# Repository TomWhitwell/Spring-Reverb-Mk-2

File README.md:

## Spring Reverb Mk 2

These are the design files for the Music Thing Modular Spring Reverb. 

[Full details about the module are in this rather long Medium post](https://medium.com/music-thing-modular-notes/everything-i-know-about-spring-reverb-1fb4b32abf87) 

You can [buy full kits for the Spring module here at Thonk](https://www.thonk.co.uk/shop/mtm-spring-reverb-mkii-kit/?utm_source=github), and [here's the kit for the expander](https://www.thonk.co.uk/shop/mtm-spring-expander-kit/?utm_source=github). 

# Issues and troubleshooting 
The quickest way to find solutions or report issues is [here in the issue log](https://github.com/TomWhitwell/Spring-Reverb-Mk-2/issues)

# In this repository you will find: 

[The Schematic PDF is here](https://github.com/TomWhitwell/Spring-Reverb-Mk-2/raw/master/Collateral/SpringReverbMk2-Schematic.pdf) 

Eagle CAD PCB files for:  
1. The main module, which contains two PCBs in the same file: SpringReverbRev2_combined
2. A plain PCB panel for the main module: SpringReverbRev2_panel
3. The PCB for the expander: Spring_Rev2_expander
4. A plan PCB panel for the expander: Spring_Rev2_expander_panel

The draft BOM is [here on google drive](https://docs.google.com/spreadsheets/d/1CzZeQc7hFVf5DQ_6vUL5soYb9Bh4oqvPB2Zx_D7NQ_I/edit?usp=sharing)

# License

Spring is Open Hardware
All hardware and software design in this project is Creative Commons licensed by Tom Whitwell: CC-BY-SA: Attribution / ShareAlike
If you use any work in this project, you should credit me, and you must republish any changes you make under the same license.
This license does permit commercial use of these designs, but consider getting in touch before selling anything.
This license does not permit you to use the name Music Thing Modular. Please do not use the name 'Spring' or 'Music Thing Modular' for any derivative works.

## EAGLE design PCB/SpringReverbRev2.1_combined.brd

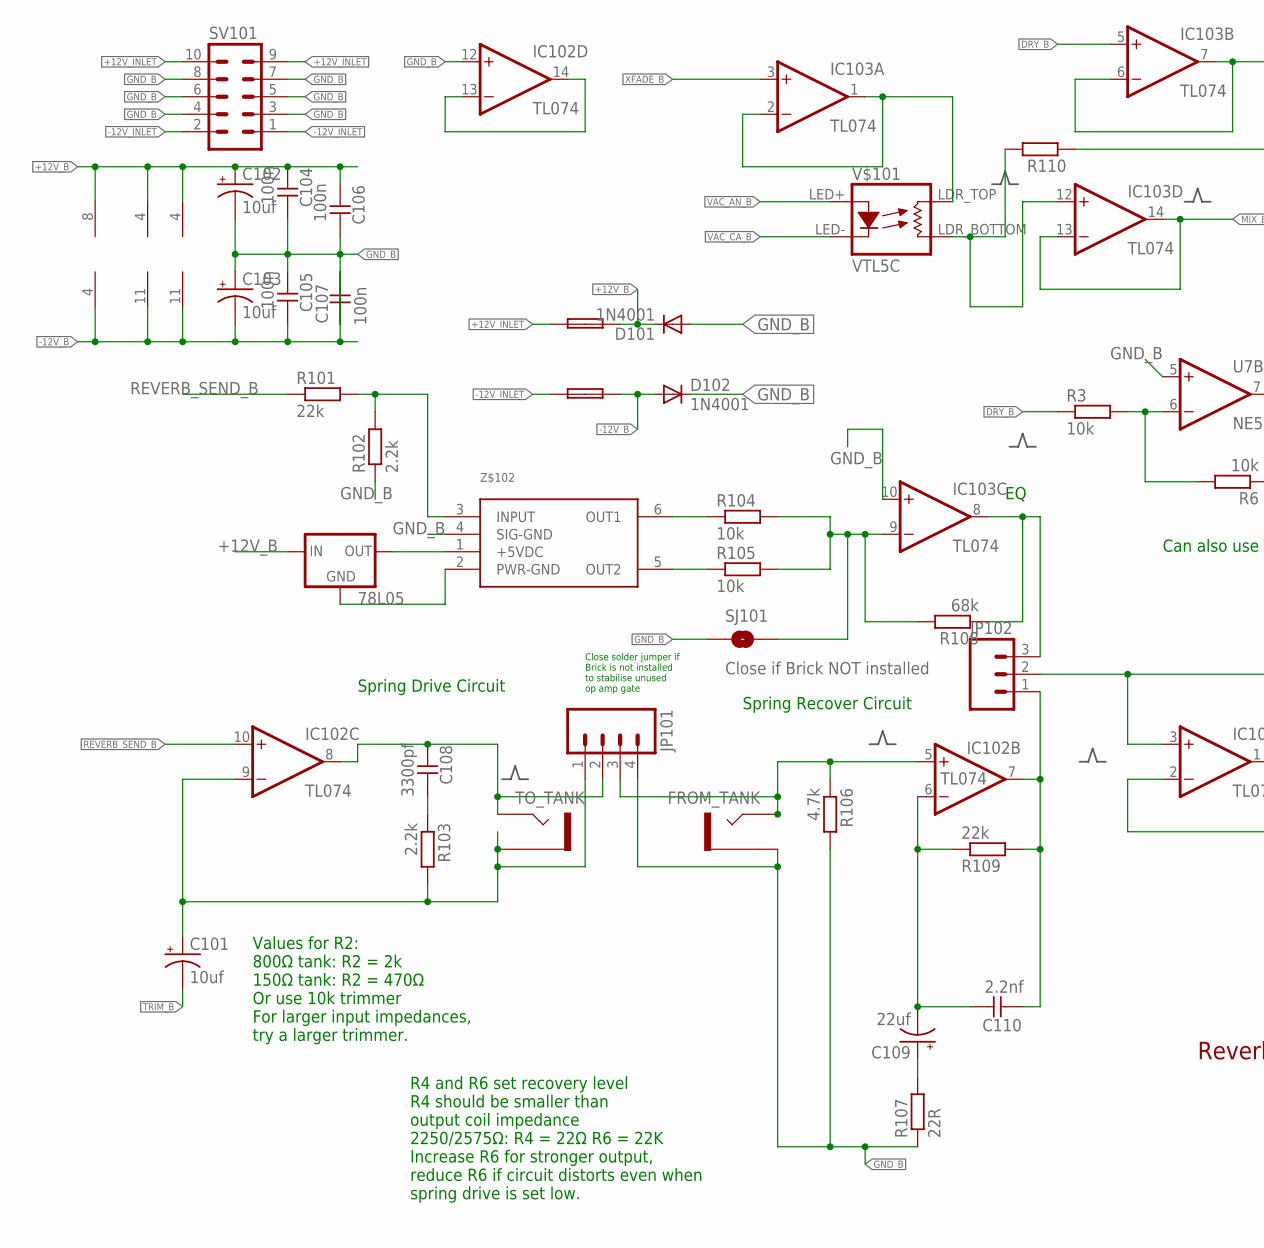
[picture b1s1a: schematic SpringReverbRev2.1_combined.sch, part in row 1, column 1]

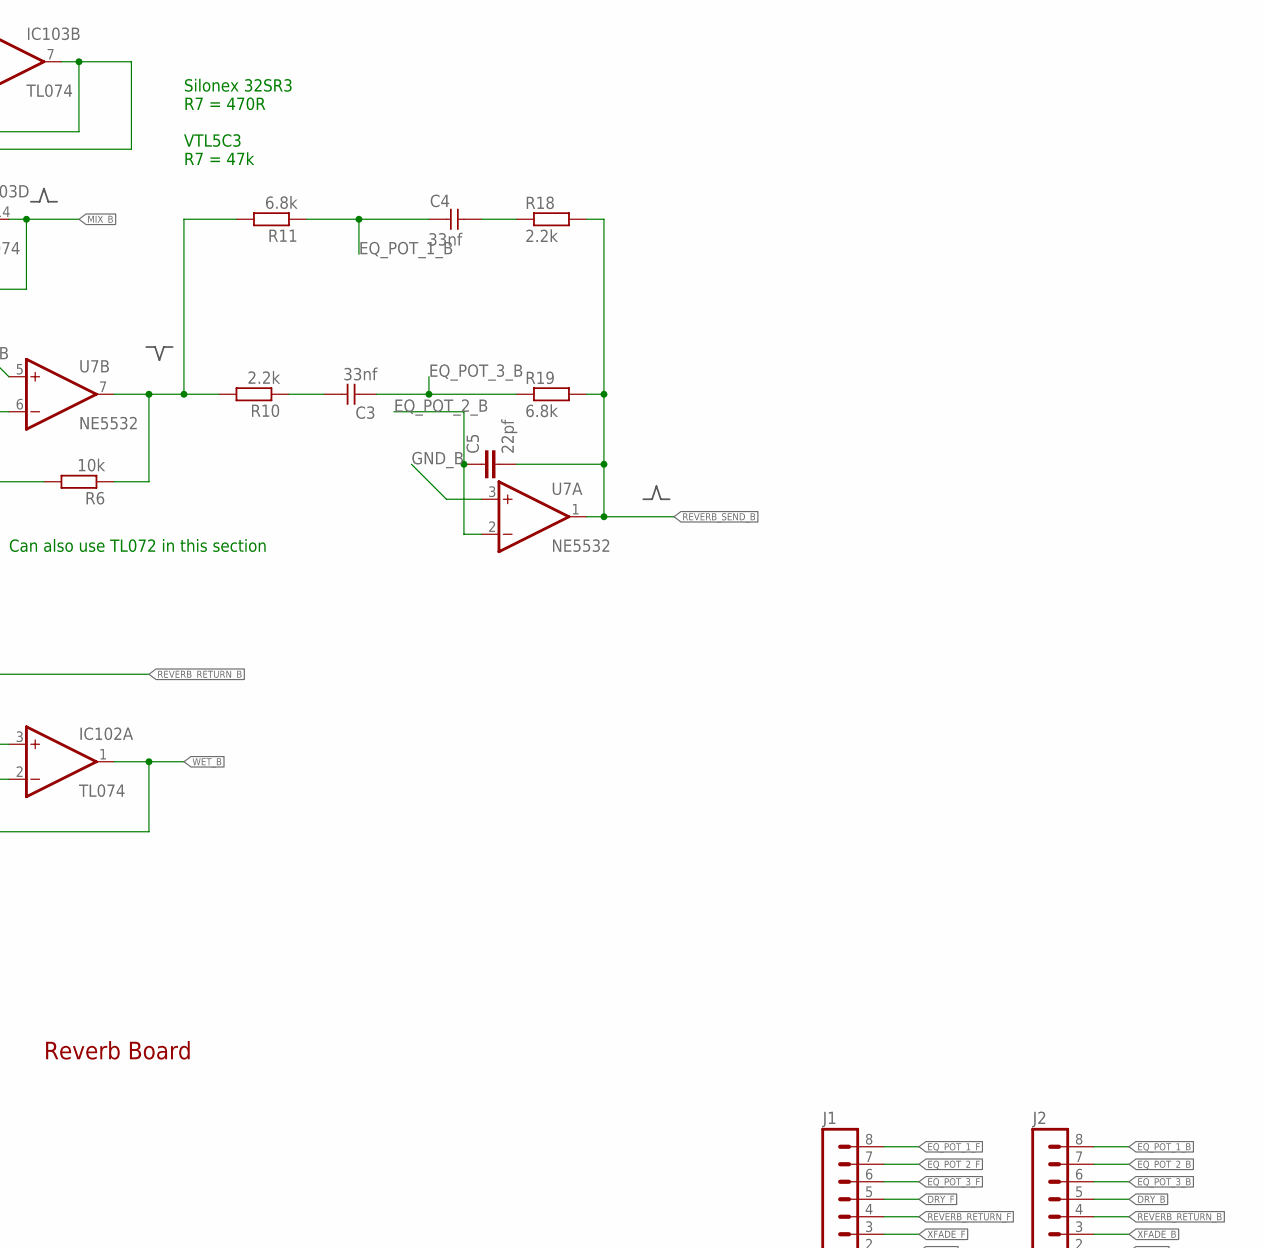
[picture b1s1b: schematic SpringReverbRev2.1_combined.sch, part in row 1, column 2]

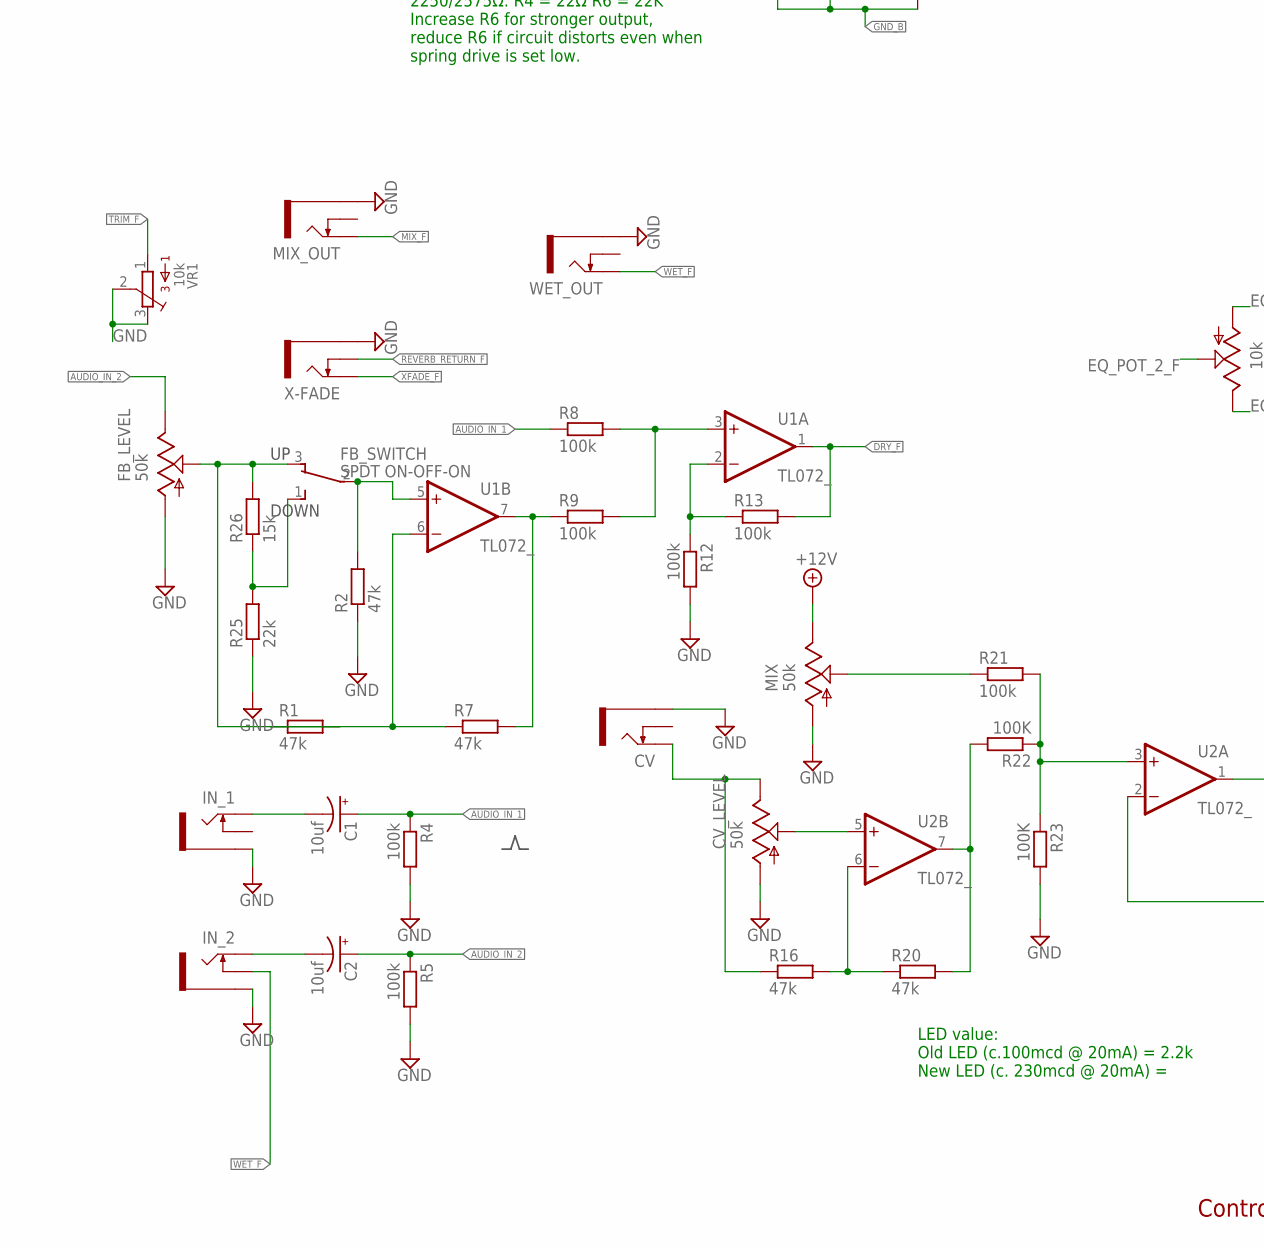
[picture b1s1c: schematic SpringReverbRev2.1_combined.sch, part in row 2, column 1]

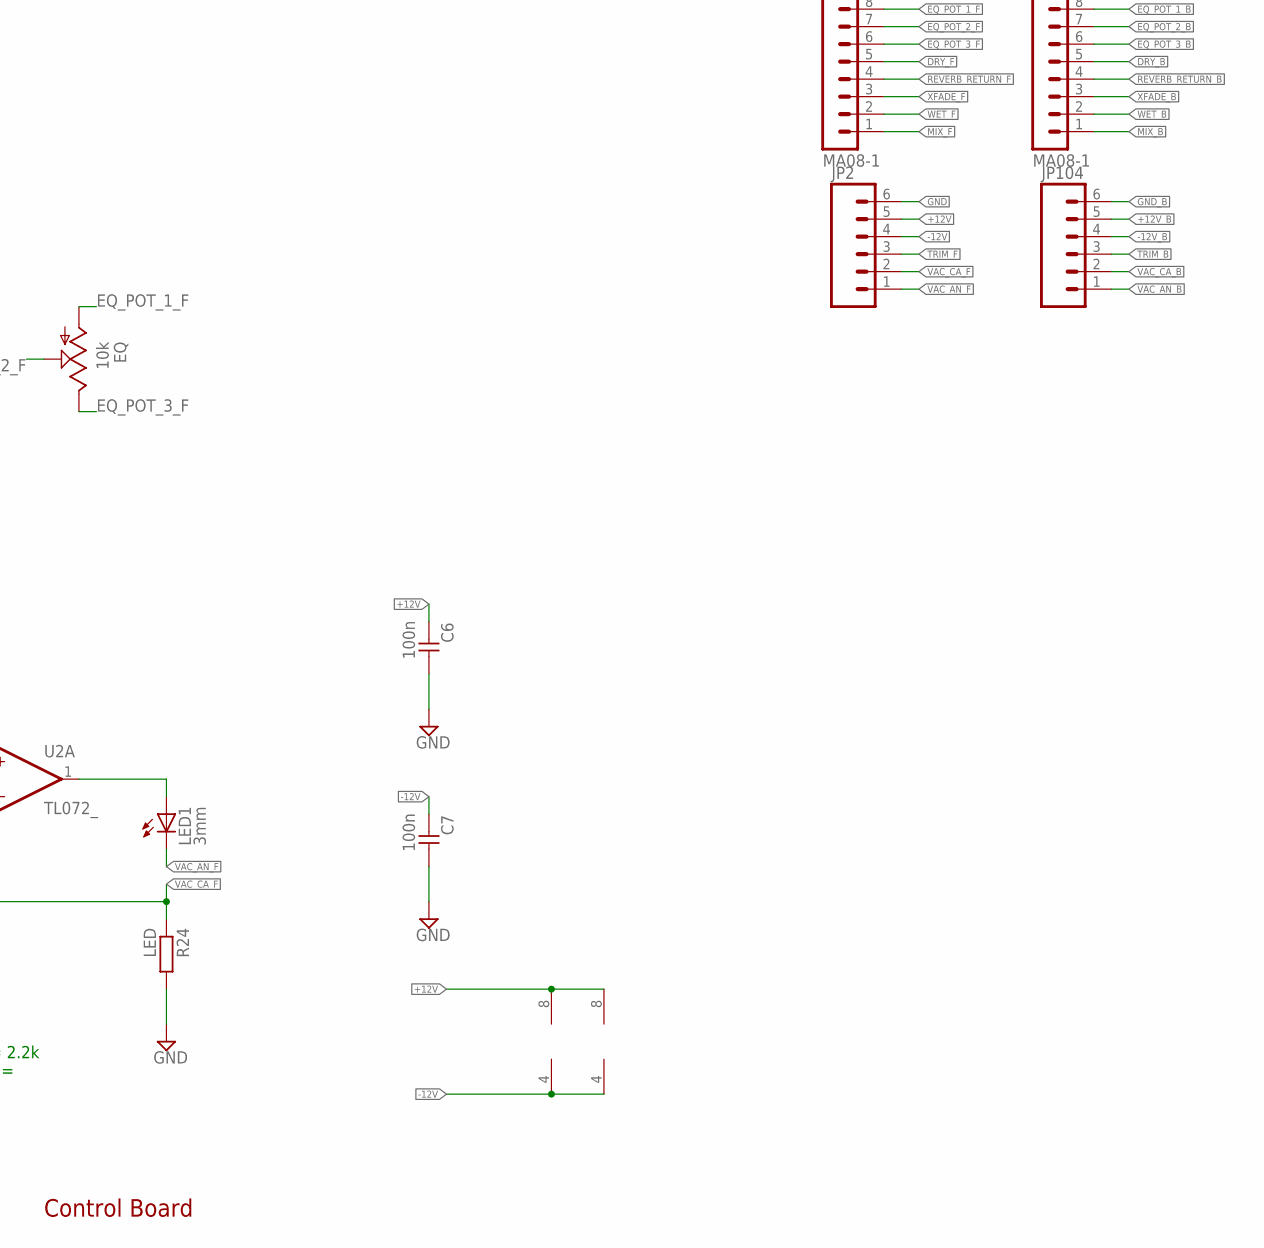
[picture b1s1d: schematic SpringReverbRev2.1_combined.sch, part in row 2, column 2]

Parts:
78L05: 78LXX
C1, C2: 10uf; 050_020
C3, C4: 33nf; C050-024X044
C5: 22pf; 050X030_025
C6, C7, C104, C105, C106, C107: 100n; C050-024X044
C101, C102, C103: 10uf; CPOL-RADIAL-10UF-25V
C108: 3300pf; C050-024X044
C109: 22uf; CPOL-RADIAL-10UF-25V
C110: 2.2nf; C050-024X044
CV: THONKICONNNEW; WQP-PJ301M-12_JACK
CV_LEVEL: 50k; EVUF
D101, D102: 1N4001; DO41-10
EQ: 10k; EVUF
F101, F102: FUSE; C050H075X075
FB_LEVEL: 50k; EVUF
FB_SWITCH: SPDT ON-OFF-ON; SPDT-VERTICAL-TOP-SUBMINI-MULTICOMP
FROM_TANK: CUI-RCJ_RCA_PHONO
IC102, IC103: TL074; DIL14
IN_1, IN_2: THONKICONNNEW; WQP-PJ301M-12_JACK
J1, J2: MA08-1
JP2, JP104: M06SIP; 1X06
JP101: M04POLAR; MOLEX-1X4
JP102: M03LOCK_NO_SILK; 1X03_LOCK_NO_SILK
LED1: 3mm; LED3MM
MIX: 50k; EVUF
MIX_OUT: THONKICONNNEW; WQP-PJ301M-12_JACK
R1, R2, R7, R16, R20: 47k; 7MM_RESISTOR
R3, R6, R104, R105: 10k; 7MM_RESISTOR
R4, R5, R8, R9, R12, R13, R21: 100k; 7MM_RESISTOR
R10, R18, R102, R103: 2.2k; 7MM_RESISTOR
R11, R19: 6.8k; 7MM_RESISTOR
R22, R23: 100K; 7MM_RESISTOR
R24: LED; 7MM_RESISTOR
R25, R101, R109: 22k; 7MM_RESISTOR
R26: 15k; 7MM_RESISTOR
R106: 4.7k; 7MM_RESISTOR
R107: 22R; 7MM_RESISTOR
R108: 68k; 7MM_RESISTOR
R110: RESISTOR7MM; 7MM_RESISTOR
SJ101: Close if Brick NOT installed; SJ_2S-NOTRACE
SV101: 10_PIN_HEADER; MA05-2
TO_TANK: CUI-RCJ_RCA_PHONO
U1, U2: TL072_; DIL08
U7: NE5532; DIL08
V$101: VTL5C; VACTROL_COMPACT
VR1: 10k; BOURNS_3362P_TRIMMER
WET_OUT: THONKICONNNEW; WQP-PJ301M-12_JACK
X-FADE: THONKICONNNEW; WQP-PJ301M-12_JACK
Z$102: BTDR-2H

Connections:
+12V: C6.2, JP2.5, MIX.3 (E), U1.8 (V+), U2.8 (V+)
+12V_B: 78L05.IN, C102.1 (+), C104.2, C106.2, D101.C, F101.1, IC102.4 (V+), IC103.4 (V+), JP104.5, U7.8 (V+)
+12V_INLET: F101.2, SV101.9, SV101.10
-12V: C7.2, JP2.4, U1.4 (V-), U2.4 (V-)
-12V_B: C103.2 (-), C105.1, C107.1, D102.A, F102.1, IC102.11 (V-), IC103.11 (V-), JP104.4, U7.4 (V-)
-12V_INLET: F102.2, SV101.1, SV101.2
AUDIO_IN_1: C1.+, R4.1, R8.1
AUDIO_IN_2: C2.+, FB_LEVEL.3 (E), R5.1
AUDIO_IN_BUF: IC103.6 (-IN), IC103.7 (OUT), R110.1
BRK: IC103.8 (OUT), JP102.3, R108.1
CV_F: R20.2, R22.2, U2.7 (OUT)
DRY_B: IC103.5 (+IN), J2.5, R3.1
DRY_F: J1.5, R13.2, U1.1 (OUT)
EQ_POT_1_B: C4.2, J2.8, R11.1
EQ_POT_1_F: EQ.1 (A), J1.8
EQ_POT_2_B: C5.1, J2.7, U7.2 (-IN)
EQ_POT_2_F: EQ.2 (S), J1.7
EQ_POT_3_B: C3.2, J2.6, R19.1
EQ_POT_3_F: EQ.3 (E), J1.6
GND: C6.1, C7.1, CV.P$3_SLEEVE (SLEEVE), CV_LEVEL.1 (A), FB_LEVEL.1 (A), IN_1.P$3_SLEEVE (SLEEVE), IN_2.P$3_SLEEVE (SLEEVE), JP2.6, MIX.1 (A), MIX_OUT.P$3_SLEEVE (SLEEVE), R2.1, R4.2, R5.2, R12.2, R23.2, R24.2, R25.1, VR1.2, VR1.3, WET_OUT.P$3_SLEEVE (SLEEVE), X-FADE.P$3_SLEEVE (SLEEVE)
GND_B: C102.2 (-), C103.1 (+), C104.1, C105.2, C106.1, C107.2, D101.A, D102.C, FROM_TANK.GND1 (SLEEVE), FROM_TANK.GND2 (SLEEVE), IC102.12 (+IN), IC103.10 (+IN), JP101.4, JP104.6, R102.1, R106.2, R107.1, SJ101.1, SV101.3, SV101.4, SV101.5, SV101.6, SV101.7, SV101.8, U7.3 (+IN), U7.5 (+IN), Z$102.4 (SIG-GND)
MIX_B: IC103.13 (-IN), IC103.14 (OUT), J2.1
MIX_F: J1.1, MIX_OUT.P$1_TIP (TIP)
unnamed: C1.-, IN_1.P$1_TIP (TIP)
unnamed: C2.-, IN_2.P$1_TIP (TIP)
unnamed: MIX.2 (S), R21.1
unnamed: FB_LEVEL.2 (S), FB_SWITCH.3, R1.2, R26.2
unnamed: R1.1, R7.1, U1.6 (-IN)
unnamed: R7.2, R9.1, U1.7 (OUT)
unnamed: R8.2, R9.2, U1.3 (+IN)
unnamed: R21.2, R22.1, R23.1, U2.3 (+IN)
unnamed: R12.1, R13.1, U1.2 (-IN)
unnamed: CV.P$1_TIP (TIP), CV_LEVEL.3 (E), R16.1
unnamed: LED1.A, U2.1 (OUT)
unnamed: FB_SWITCH.1, R25.2, R26.1
unnamed: C3.1, R10.1
unnamed: C109.1 (+), R107.2
unnamed: C109.2 (-), C110.1, IC102.6 (-IN), R109.1
unnamed: CV_LEVEL.2 (S), U2.5 (+IN)
unnamed: C4.1, R18.1
unnamed: R16.2, R20.1, U2.6 (-IN)
unnamed: R3.2, R6.2, U7.6 (-IN)
unnamed: C108.1, R103.1
unnamed: 78L05.OUT, Z$102.1 (+5VDC)
unnamed: R104.1, Z$102.6 (OUT1)
unnamed: R105.1, Z$102.5 (OUT2)
unnamed: IC103.9 (-IN), R104.2, R105.2, R108.2, SJ101.2
unnamed: R6.1, R10.2, R11.2, U7.7 (OUT)
unnamed: R101.2, R102.2, Z$102.3 (INPUT)
unnamed: 78L05.GND, Z$102.2 (PWR-GND)
unnamed: IC103.12 (+IN), R110.2, V$101.LDR_BOTTOM (RES2)
unnamed: IC102.13 (-IN), IC102.14 (OUT)
unnamed: FB_SWITCH.2, R2.2, U1.5 (+IN)
R+: FROM_TANK.+V (TIP), IC102.5 (+IN), JP101.3, R106.1
REVERB_RETURN_B: IC102.3 (+IN), J2.4, JP102.2
REVERB_RETURN_F: J1.4, X-FADE.P$2_SWITCH (SWITCH)
REVERB_SEND_B: C5.2, IC102.10 (+IN), R18.2, R19.2, R101.1, U7.1 (OUT)
S+: C101.1 (+), IC102.9 (-IN), JP101.1, R103.2, TO_TANK.GND1 (SLEEVE), TO_TANK.GND2 (SLEEVE)
S-: C108.2, IC102.8 (OUT), JP101.2, TO_TANK.+V (TIP)
SPNG: C110.2, IC102.7 (OUT), JP102.1, R109.2
TRIM_B: C101.2 (-), JP104.3
TRIM_F: JP2.3, VR1.1
VAC_AN_B: JP104.1, V$101.LED+
VAC_AN_F: JP2.1, LED1.K (C)
VAC_CA_B: JP104.2, V$101.LED-
VAC_CA_F: JP2.2, R24.1, U2.2 (-IN)
WET_B: IC102.1 (OUT), IC102.2 (-IN), J2.2
WET_F: IN_2.P$2_SWITCH (SWITCH), J1.2, WET_OUT.P$1_TIP (TIP)
XFADE_B: IC103.3 (+IN), J2.3
XFADE_F: J1.3, X-FADE.P$1_TIP (TIP)
X_FADE_IN: IC103.1 (OUT), IC103.2 (-IN), V$101.LDR_TOP (RES1)

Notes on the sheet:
Control Board
Can also use TL072 in this section
Values for R2: 800Ω tank: R2 = 2k 150Ω tank: R2 = 470Ω Or use 10k trimmer For larger input impedances, try a larger trimmer.
Spring Drive Circuit
R4 and R6 set recovery level R4 should be smaller than output coil impedance 2250/2575Ω: R4 = 22Ω R6 = 22K Increase R6 for stronger output, reduce R6 if circuit distorts even when spring drive is set low.
Spring Recover Circuit
Reverb Board
Silonex 32SR3 R7 = 470R VTL5C3 R7 = 47k
Close solder jumper if Brick is not installed to stabilise unused op amp gate
LED value: Old LED (c.100mcd @ 20mA) = 2.2k New LED (c. 230mcd @ 20mA) =

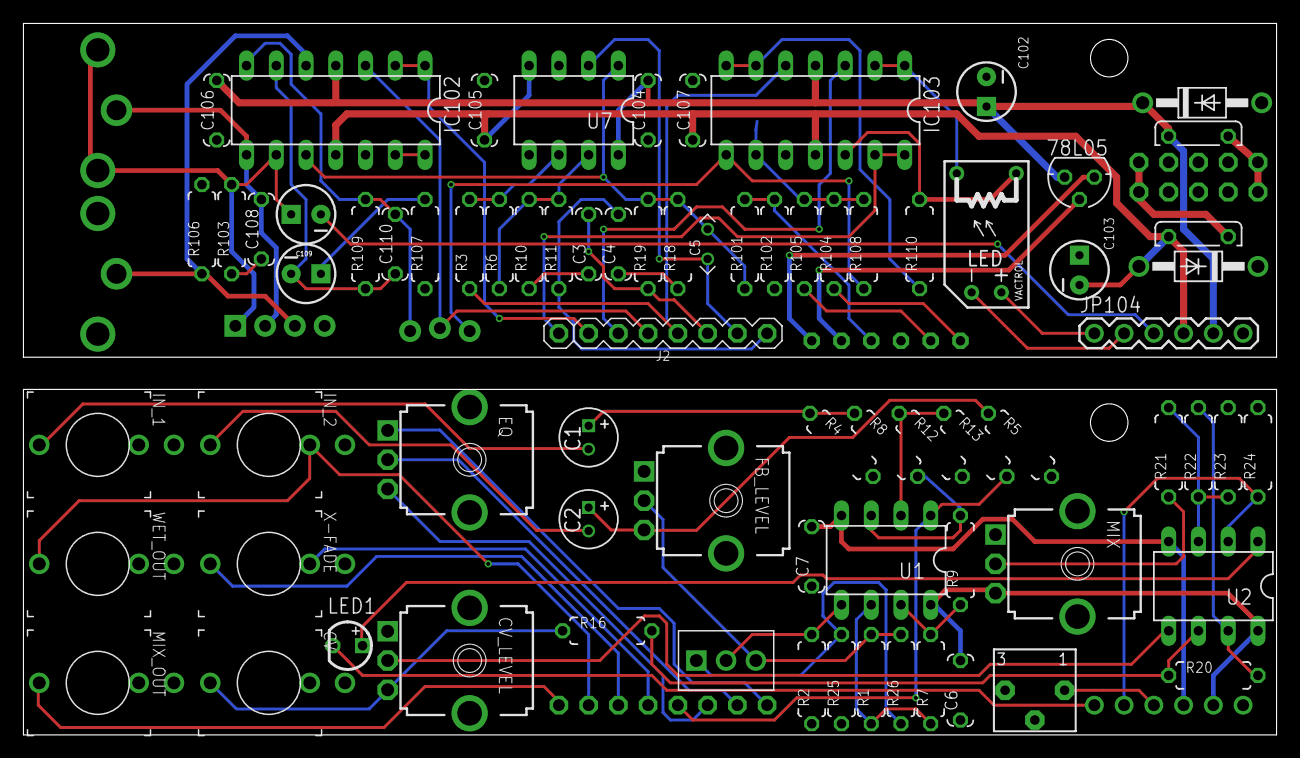
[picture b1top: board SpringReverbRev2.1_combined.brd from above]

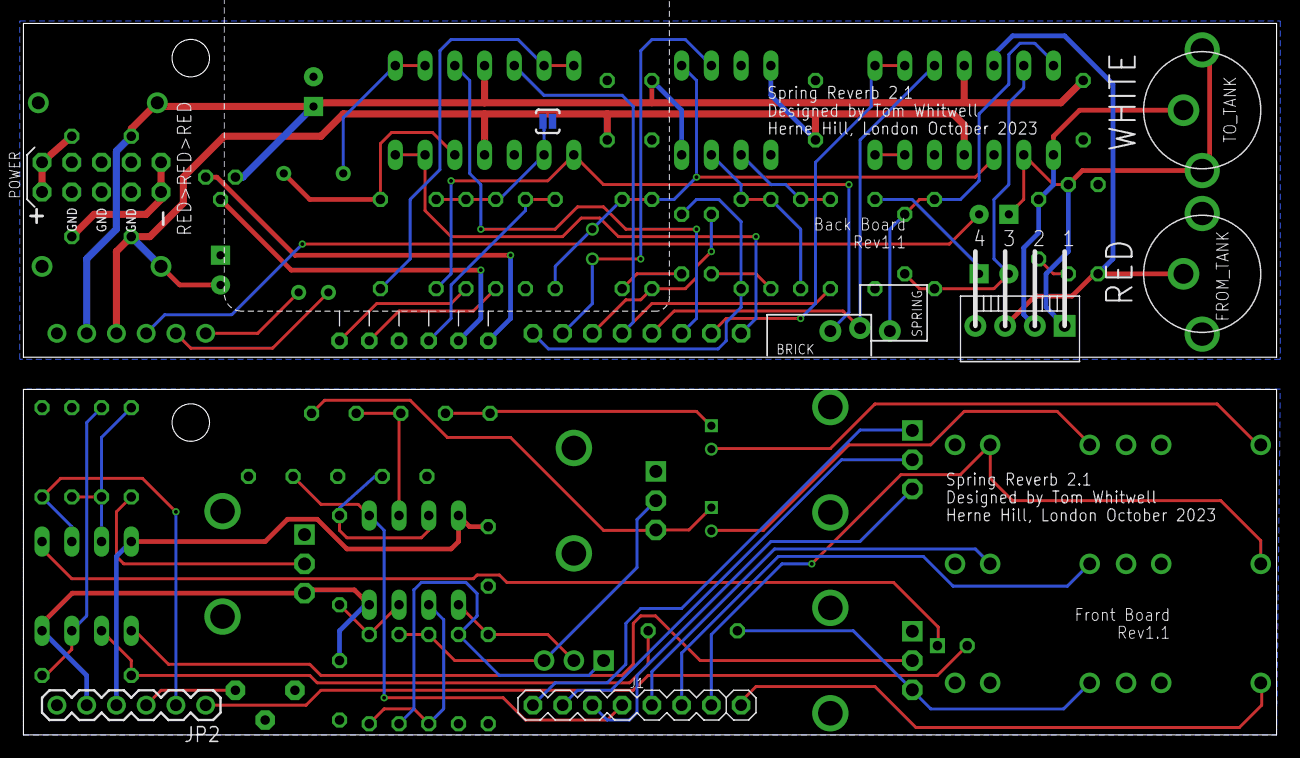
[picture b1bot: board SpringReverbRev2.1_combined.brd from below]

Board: 2 copper layers, 107.0 x 60.8 mm, 87 parts (9 on the bottom side), 71 nets.

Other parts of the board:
U$3, U$4: MOUNTING_HOLE

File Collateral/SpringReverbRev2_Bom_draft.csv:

"Qty";"Value";"Device";"Package";"Parts";"Description";"MF";"MPN";"OC_FARNELL";"OC_NEWARK";"SPICE";
"1";"";"10_PIN_HEADER";"MA05-2";"SV101";"PIN HEADER";"";"";"unknown";"unknown";"";
"1";"";"78LXX";"78LXX";"78L05";"VOLTAGE REGULATOR";"";"";"";"";"";
"1";"";"BTDR-2H";"BTDR-2H";"Z$102";"Accutronics BTDR-2H";"";"";"";"";"";
"1";"";"M03LOCK_NO_SILK";"1X03_LOCK_NO_SILK";"JP102";"Header 3";"";"";"";"";"";
"1";"";"M04POLAR";"MOLEX-1X4";"JP101";"Header 4";"";"";"";"";"";
"2";"";"M06SIP";"1X06";"JP2, JP104";"Header 6";"";"";"";"";"";
"1";"";"RESISTOR7MM";"7MM_RESISTOR";"R110";"Standard resistor, various versions";"";"";"";"";"";
"2";"100K";"RESISTOR7MM";"7MM_RESISTOR";"R22, R23";"Standard resistor, various versions";"";"";"";"";"";
"7";"100k";"RESISTOR7MM";"7MM_RESISTOR";"R4, R5, R8, R9, R12, R13, R21";"Standard resistor, various versions";"";"";"";"";"";
"6";"100n";"C-EU050-024X044";"C050-024X044";"C6, C7, C104, C105, C106, C107";"CAPACITOR, European symbol";"";"";"";"";"";
"1";"10k";"ALPHA-9MMF2A";"EVUF";"EQ";"9 mm Square Rotary Potentiometers";"";"";"";"";"";
"1";"10k";"BOURNS_3362P_TRIMMERP";"BOURNS_3362P_TRIMMER";"VR1";"3362 Series";"";"";"";"";"";
"4";"10k";"RESISTOR7MM";"7MM_RESISTOR";"R3, R6, R104, R105";"Standard resistor, various versions";"";"";"";"";"";
"2";"10uf";"050";"050_020";"C1, C2";"0.22 - 100uF";"";"";"";"";"";
"3";"10uf";"CAP_POLPTH2";"CPOL-RADIAL-10UF-25V";"C101, C102, C103";"Capacitor Polarized";"";"";"";"";"";
"1";"15k";"RESISTOR7MM";"7MM_RESISTOR";"R26";"Standard resistor, various versions";"";"";"";"";"";
"2";"1N4001";"1N4004";"DO41-10";"D101, D102";"DIODE";"";"";"";"";"";
"5";"2.2k";"RESISTOR7MM";"7MM_RESISTOR";"R10, R18, R24, R102, R103";"Standard resistor, various versions";"";"";"";"";"";
"1";"2.2nf ";"C-EU050-024X044";"C050-024X044";"C110";"CAPACITOR, European symbol";"";"";"";"";"";
"1";"22R";"RESISTOR7MM";"7MM_RESISTOR";"R107";"Standard resistor, various versions";"";"";"";"";"";
"3";"22k";"RESISTOR7MM";"7MM_RESISTOR";"R25, R101, R109";"Standard resistor, various versions";"";"";"";"";"";
"1";"22pf";"050X030_0251";"050X030_025";"C5";"47 - 120pF";"";"";"";"";"";
"1";"22uf";"CAP_POLPTH2";"CPOL-RADIAL-10UF-25V";"C109";"Capacitor Polarized";"";"";"";"";"";
"1";"3300pf";"C-EU050-024X044";"C050-024X044";"C108";"CAPACITOR, European symbol";"";"";"";"";"";
"2";"33nf";"C-EU050-024X044";"C050-024X044";"C3, C4";"CAPACITOR, European symbol";"";"";"";"";"";
"1";"3mm";"LED3MM";"LED3MM";"LED1";"LED";"";"";"";"";"";
"1";"4.7k";"RESISTOR7MM";"7MM_RESISTOR";"R106";"Standard resistor, various versions";"";"";"";"";"";
"5";"47k";"RESISTOR7MM";"7MM_RESISTOR";"R1, R2, R7, R16, R20";"Standard resistor, various versions";"";"";"";"";"";
"3";"50k";"ALPHA-9MMF2A";"EVUF";"CV_LEVEL, FB_LEVEL, MIX";"9 mm Square Rotary Potentiometers";"";"";"";"";"";
"2";"6.8k";"RESISTOR7MM";"7MM_RESISTOR";"R11, R19";"Standard resistor, various versions";"";"";"";"";"";
"1";"68k";"RESISTOR7MM";"7MM_RESISTOR";"R108";"Standard resistor, various versions";"";"";"";"";"";
"1";"Close if Brick NOT installed";"SOLDERJUMPERNC2";"SJ_2S-NOTRACE";"SJ101";"Solder Jumper";"";"";"";"";"";
"1";"FROM_TANK";"BTOR1";"BTOR1";"X102";"RCA connectors according to JEITA RC-5231 Cinch";"";"BTOR 1";"1217030";"96K7172";"";
"2";"FUSE";"PTC_FUSEPOLY_FUSE";"C050H075X075";"F101, F102";"";"";"";"";"";"";
"2";"MA08-1";"MA08-1";"MA08-1";"J1, J2";"Pin Header";"";"";"";"";"";
"1";"NE5532";"TL072_";"DIL08";"U7";"Generic Dual Op Amp";"";"";"";"";"";
"1";"SPDT ON-OFF-ON";"SPDT-VERTICAL-UPTOP-SUBMINI";"SPDT-VERTICAL-TOP-SUBMINI-MULTICOMP";"FB_SWITCH";"Vertical SPDT switch in the up position.";"";"";"";"";"R{NAME} {2.NET} {3.NET} 1";
"6";"THONKICONNNEW";"THONKICONNNEW";"WQP-PJ301M-12_JACK";"CV, IN_1, IN_2, MIX_OUT, WET_OUT, X-FADE";"3.5mm socket for Eurorack modular synths";"";"";"";"";"";
"2";"TL072_";"TL072_";"DIL08";"U1, U2";"Generic Dual Op Amp";"";"";"";"";"";
"2";"TL074";"TL074P";"DIL14";"IC102, IC103";"OP AMP";"";"";"";"";"";
"1";"TO_TANK";"BTOR1";"BTOR1";"X101";"RCA connectors according to JEITA RC-5231 Cinch";"";"BTOR 1";"1217030";"96K7172";"";
"1";"VTL5C";"VACTROL_COMPACT";"VACTROL_COMPACT";"V$101";"";"";"";"";"";"";

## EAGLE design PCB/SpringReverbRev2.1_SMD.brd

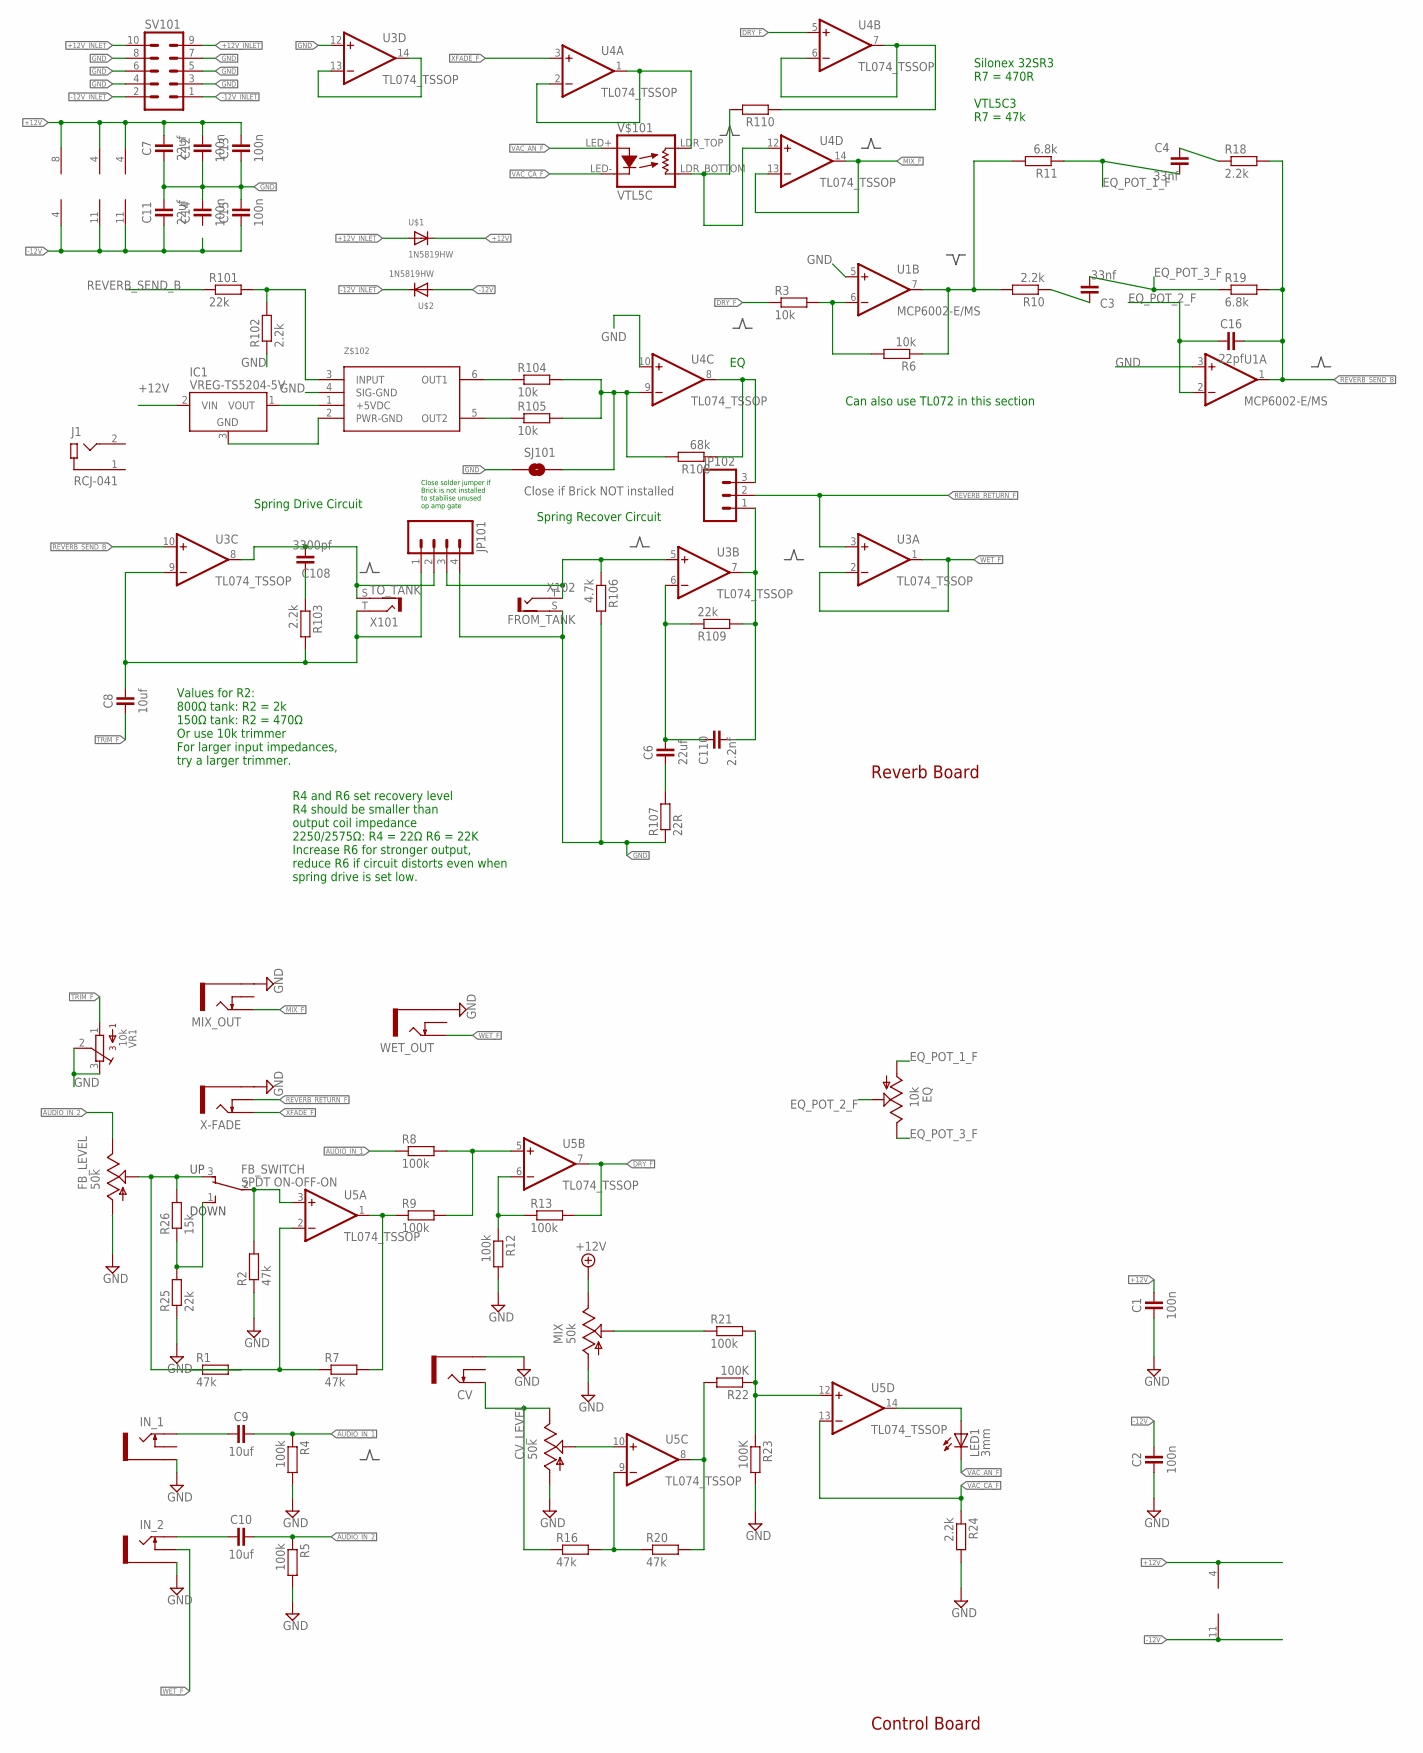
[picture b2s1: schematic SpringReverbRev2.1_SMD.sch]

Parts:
C1, C2, C12, C13, C14, C15: 100n; C0402
C3, C4: 33nf; C0402
C6: 22uf; C1210
C7, C11: 22uf; C1206
C8, C9, C10: 10uf; C0805
C16: 22pf; C0402
C108: 3300pf; C0402
C110: 2.2nf; C0402
CV: THONKICONNNEW; WQP-PJ301M-12_JACK
CV_LEVEL: 50k; EVUF
EQ: 10k; EVUF
FB_LEVEL: 50k; EVUF
FB_SWITCH: SPDT ON-OFF-ON; SPDT-VERTICAL-TOP-SUBMINI-MULTICOMP
IC1: VREG-TS5204-5V; SOT23
IN_1, IN_2: THONKICONNNEW; WQP-PJ301M-12_JACK
J1: RCJ-041
JP101: M04POLAR; MOLEX-1X4
JP102: M03LOCK_NO_SILK; 1X03_LOCK_NO_SILK
LED1: 3mm; LED3MM
MIX: 50k; EVUF
MIX_OUT: THONKICONNNEW; WQP-PJ301M-12_JACK
R1, R2, R7, R16, R20: 47k; C0402
R3, R6, R104, R105: 10k; C0402
R4, R5, R8, R9, R12, R13, R21: 100k; C0402
R10, R18, R24, R102, R103: 2.2k; C0402
R11, R19: 6.8k; C0402
R22, R23: 100K; C0402
R25, R101, R109: 22k; C0402
R26: 15k; C0402
R106: 4.7k; C0402
R107: 22R; C0402
R108: 68k; C0402
R110: RESISTOR-0402; C0402
SJ101: Close if Brick NOT installed; SJ_2S-NOTRACE
SV101: 10_PIN_HEADER; MA05-2
U1: MCP6002-E/MS; SOP65P490X110-8N
U3, U4, U5: TL074_TSSOP; SOP65P640X120-14N
U$1, U$2: 1N5819HW; SOD-123-EDITED
V$101: VTL5C; VACTROL_COMPACT
VR1: 10k; BOURNS_3362P_TRIMMER
WET_OUT: THONKICONNNEW; WQP-PJ301M-12_JACK
X101: TO_TANK; BTOR1
X102: FROM_TANK; BTOR1
X-FADE: THONKICONNNEW; WQP-PJ301M-12_JACK
Z$102: BTDR-2H

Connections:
+12V: C1.2, C7.2, C12.2, C13.2, IC1.2 (VIN), MIX.3 (E), U1.8 (V+), U3.4 (V+), U4.4 (V+), U5.4 (V+), U$1.C
+12V_INLET: SV101.9, SV101.10, U$1.A
-12V: C2.2, C11.1, C15.1, U1.4 (V-), U3.11 (V-), U4.11 (V-), U5.11 (V-), U$2.A
-12V_INLET: SV101.1, SV101.2, U$2.C
AUDIO_IN_1: C9.2, R4.1, R8.1
AUDIO_IN_2: C10.2, FB_LEVEL.3 (E), R5.1
AUDIO_IN_BUF: R110.1, U4.6 (-IN), U4.7 (OUT)
BRK: JP102.3, R108.1, U4.8 (OUT)
CV_F: R20.2, R22.2, U5.8 (OUT)
DRY_F: R3.1, R13.2, U4.5 (+IN), U5.7 (OUT)
EQ_POT_1_F: C4.2, EQ.1 (A), R11.1
EQ_POT_2_F: C16.1, EQ.2 (S), U1.2 (-IN)
EQ_POT_3_F: C3.2, EQ.3 (E), R19.1
GND: C1.1, C2.1, C7.1, C11.2, C12.1, C13.1, C14.2, C15.2, CV.P$3_SLEEVE (SLEEVE), CV_LEVEL.1 (A), FB_LEVEL.1 (A), IN_1.P$3_SLEEVE (SLEEVE), IN_2.P$3_SLEEVE (SLEEVE), JP101.4, MIX.1 (A), MIX_OUT.P$3_SLEEVE (SLEEVE), R2.1, R4.2, R5.2, R12.2, R23.2, R24.2, R25.1, R102.1, R106.2, R107.1, SJ101.1, SV101.3, SV101.4, SV101.5, SV101.6, SV101.7, SV101.8, U1.3 (+IN), U1.5 (+IN), U3.12 (+IN), U4.10 (+IN), VR1.2, VR1.3, WET_OUT.P$3_SLEEVE (SLEEVE), X102.S (2), X-FADE.P$3_SLEEVE (SLEEVE), Z$102.4 (SIG-GND)
MIX_F: MIX_OUT.P$1_TIP (TIP), U4.13 (-IN), U4.14 (OUT)
unnamed: C9.1, IN_1.P$1_TIP (TIP)
unnamed: C10.1, IN_2.P$1_TIP (TIP)
unnamed: MIX.2 (S), R21.1
unnamed: FB_LEVEL.2 (S), FB_SWITCH.3, R1.2, R26.2
unnamed: R1.1, R7.1, U5.2 (-IN)
unnamed: R7.2, R9.1, U5.1 (OUT)
unnamed: R8.2, R9.2, U5.5 (+IN)
unnamed: R21.2, R22.1, R23.1, U5.12 (+IN)
unnamed: R12.1, R13.1, U5.6 (-IN)
unnamed: CV.P$1_TIP (TIP), CV_LEVEL.3 (E), R16.1
unnamed: LED1.A, U5.14 (OUT)
unnamed: FB_SWITCH.1, R25.2, R26.1
unnamed: C3.1, R10.1
unnamed: C6.1, R107.2
unnamed: C6.2, C110.1, R109.1, U3.6 (-IN)
unnamed: CV_LEVEL.2 (S), U5.10 (+IN)
unnamed: C4.1, R18.1
unnamed: R16.2, R20.1, U5.9 (-IN)
unnamed: R3.2, R6.2, U1.6 (-IN)
unnamed: C108.1, R103.1
unnamed: IC1.1 (VOUT), Z$102.1 (+5VDC)
unnamed: R104.1, Z$102.6 (OUT1)
unnamed: R105.1, Z$102.5 (OUT2)
unnamed: R104.2, R105.2, R108.2, SJ101.2, U4.9 (-IN)
unnamed: R6.1, R10.2, R11.2, U1.7 (OUT)
unnamed: R101.2, R102.2, Z$102.3 (INPUT)
unnamed: IC1.3 (GND), Z$102.2 (PWR-GND)
unnamed: R110.2, U4.12 (+IN), V$101.LDR_BOTTOM (RES2)
unnamed: U3.13 (-IN), U3.14 (OUT)
unnamed: FB_SWITCH.2, R2.2, U5.3 (+IN)
R+: JP101.3, R106.1, U3.5 (+IN), X102.T (1)
REVERB_RETURN_F: JP102.2, U3.3 (+IN), X-FADE.P$2_SWITCH (SWITCH)
REVERB_SEND_B: C16.2, R18.2, R19.2, R101.1, U1.1 (OUT), U3.10 (+IN)
S+: C8.2, JP101.1, R103.2, U3.9 (-IN), X101.T (1)
S-: C108.2, JP101.2, U3.8 (OUT), X101.S (2)
SPNG: C110.2, JP102.1, R109.2, U3.7 (OUT)
TRIM_F: C8.1, VR1.1
VAC_AN_F: LED1.K (C), V$101.LED+
VAC_CA_F: R24.1, U5.13 (-IN), V$101.LED-
WET_F: IN_2.P$2_SWITCH (SWITCH), U3.1 (OUT), U3.2 (-IN), WET_OUT.P$1_TIP (TIP)
XFADE_F: U4.3 (+IN), X-FADE.P$1_TIP (TIP)
X_FADE_IN: U4.1 (OUT), U4.2 (-IN), V$101.LDR_TOP (RES1)

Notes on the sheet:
Control Board
Can also use TL072 in this section
Values for R2: 800Ω tank: R2 = 2k 150Ω tank: R2 = 470Ω Or use 10k trimmer For larger input impedances, try a larger trimmer.
Spring Drive Circuit
R4 and R6 set recovery level R4 should be smaller than output coil impedance 2250/2575Ω: R4 = 22Ω R6 = 22K Increase R6 for stronger output, reduce R6 if circuit distorts even when spring drive is set low.
Spring Recover Circuit
Reverb Board
Silonex 32SR3 R7 = 470R VTL5C3 R7 = 47k
Close solder jumper if Brick is not installed to stabilise unused op amp gate

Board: 2 copper layers, 79 parts (7 on the bottom side), 57 nets, no tracks yet.

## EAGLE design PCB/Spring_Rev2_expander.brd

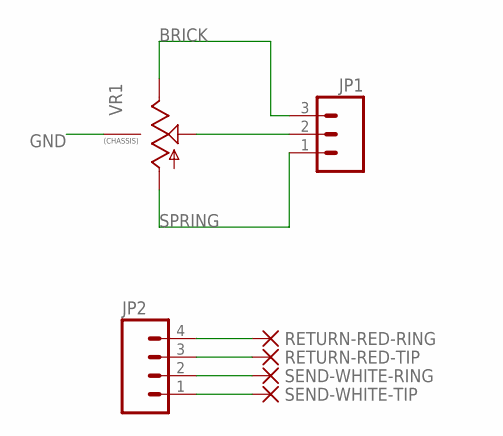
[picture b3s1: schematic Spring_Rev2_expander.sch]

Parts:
JP1: M03POLAR_LOCK; MOLEX-1X3_LOCK
JP2: M04POLAR_LOCK; MOLEX-1X4_LOCK
RETURN-RED-RING: PAD-1.00-2.00
RETURN-RED-TIP: PAD-1.00-2.00
SEND-WHITE-RING: PAD-1.00-2.00
SEND-WHITE-TIP: PAD-1.00-2.00
VR1: 9MM_SNAP-IN_POT_CHASSIS; 9MM_SNAP-IN_POT

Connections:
BRICK: JP1.3, VR1.3 (E)
GND: JP2.4, RETURN-RED-RING.1, VR1.CHASSIS1, VR1.CHASSIS2
OUT: JP1.2, VR1.2 (S)
R+: JP2.3, RETURN-RED-TIP.1
S+: JP2.1, SEND-WHITE-TIP.1
S-: JP2.2, SEND-WHITE-RING.1
SPRING: JP1.1, VR1.1 (A)

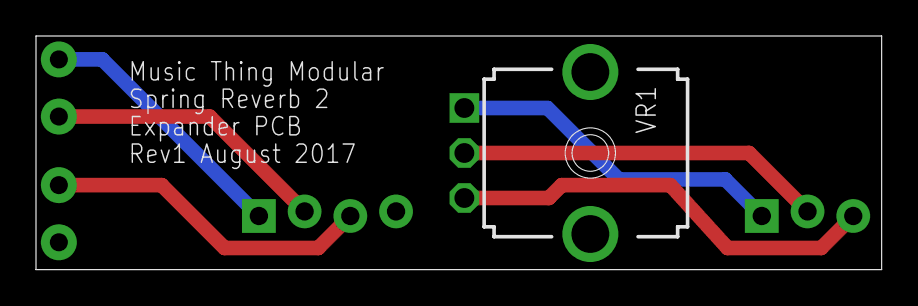
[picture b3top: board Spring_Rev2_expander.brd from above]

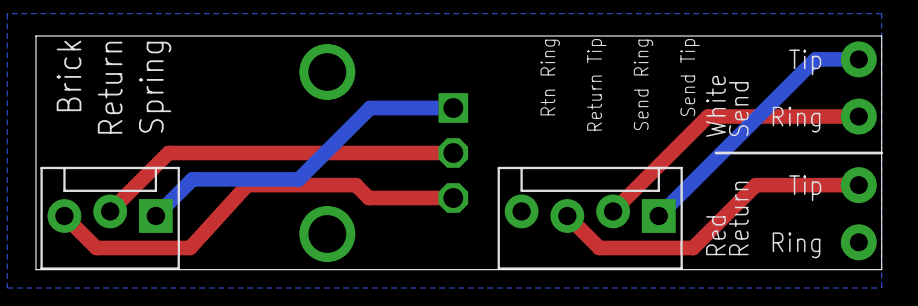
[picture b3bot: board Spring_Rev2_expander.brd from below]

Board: 2 copper layers, 47.0 x 13.0 mm, 7 parts (6 on the bottom side), 7 nets.

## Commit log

2017-11-21 Upload files
2017-11-21 remove draft bom
2023-10-03 Updated for CUI RCJ RCA Phono Jacks
2024-05-03 Fixes #18

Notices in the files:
parts and their libraries:
SparkFun-Passives: Licensing: CC v3.0 Share-Alike You are welcome to use this library for commercial purposes.
